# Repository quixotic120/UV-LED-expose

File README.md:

Controller board for a UV exposure box. Untested! Plan to support 2 layers of UV LEDs, 20x4 LCD, and a vacuum pump; ideally will be used for PCB exposure and solder mask curing.

completed:
board layout

to do:
test layout
firmware
plans for enclosure

if you try it let me know if it works!

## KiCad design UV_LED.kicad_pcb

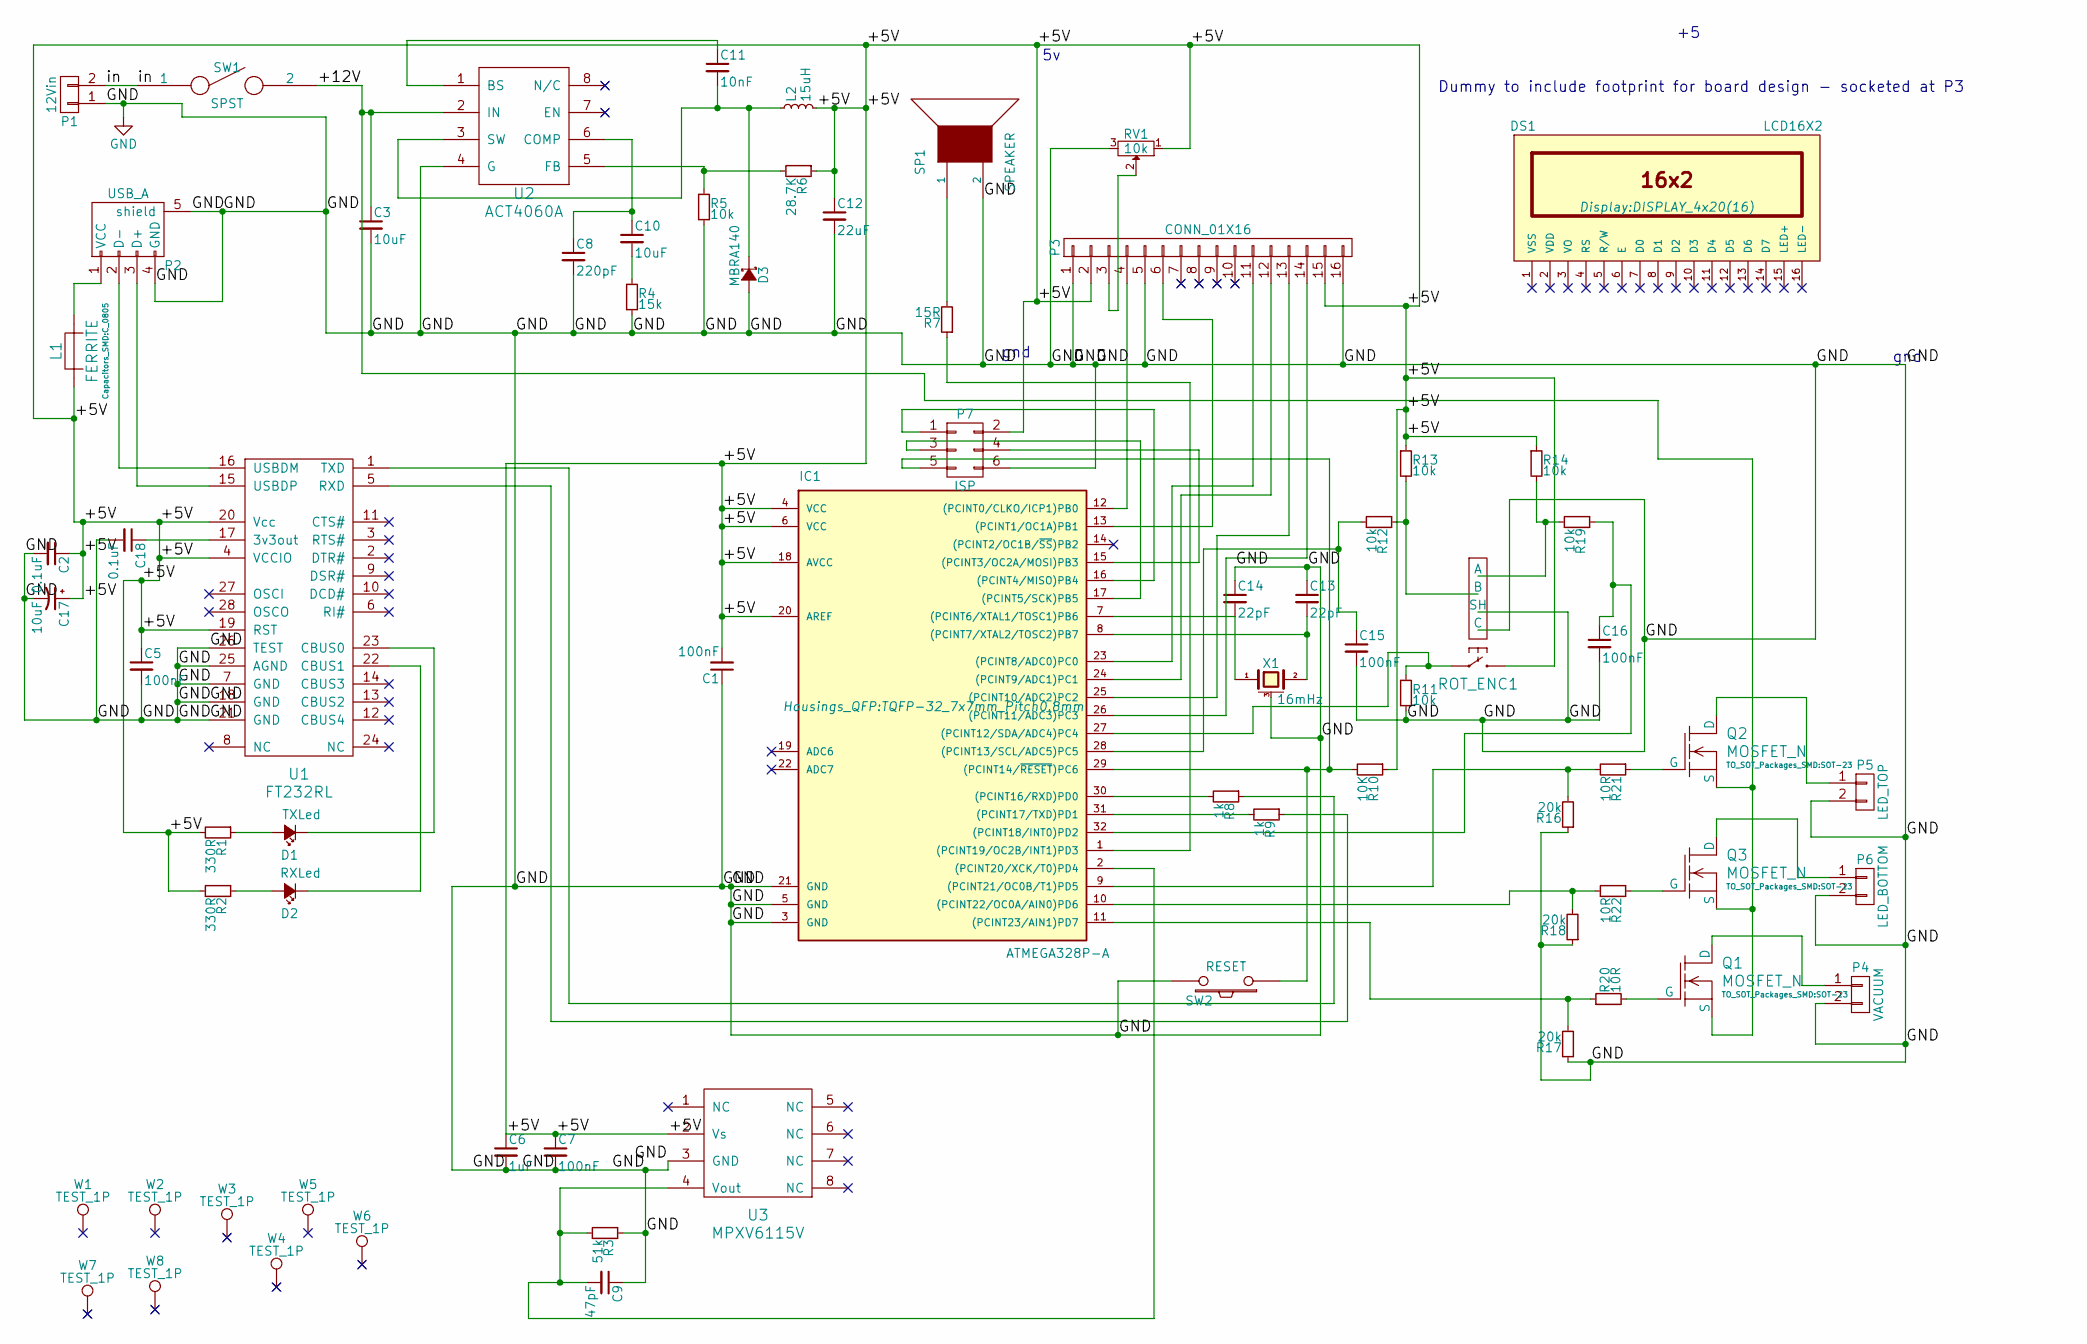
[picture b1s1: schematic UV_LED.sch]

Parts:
C1, C5, C7, C15, C16: 100nF; C_0805
C2, C18: 0.1uF; C_0805
C3, C10: 10uF; C_0805
C6: 1uF; C_0805
C8: 220pF; C_0805
C9: 47pF; C_0805
C11: 10nF; C_0805
C12: 22uF; C_0805
C13, C14: 22pF; C_0805
C17: 10uF; TantalC_SizeB_EIA-3528_Reflow
D1: TXLed; LED_0805
D2: RXLed; LED_0805
D3: MBRA140; DO-214AB
DS1: LCD16X2; DISPLAY_4x20(16)
IC1: ATMEGA328P-A; TQFP-32_7x7mm_Pitch0.8mm
L1: FERRITE; C_0805
L2: 15uH; C_0805
P1: 12Vin; Socket_MOLEX-KK-RM2-54mm_Lock_2pin_straight
P2: USB_A; USB_B
P3: CONN_01X16; Pin_Header_Angled_1x16_backward
P4: VACUUM; Socket_MOLEX-KK-RM2-54mm_Lock_2pin_straight
P5: LED_TOP; Socket_MOLEX-KK-RM2-54mm_Lock_2pin_straight
P6: LED_BOTTOM; Socket_MOLEX-KK-RM2-54mm_Lock_2pin_straight
P7: ISP; Pin_Header_Straight_2x03
Q1, Q2, Q3: MOSFET_N; SOT-23
R1, R2: 330R; R_0805
R3: 51k; R_0805
R4: 15k; R_0805
R5, R11, R12, R13, R14, R19: 10k; R_0805
R6: 28.7K; R_0805
R7: 15R; R_0805
R8, R9: 1k; R_0805
R10: 10K; R_0805
R16, R17, R18: 20k; R_0805
R20, R21, R22: 10R; R_0805
ROT_ENC1: AB2_ROTARY_ENCODER_W_SW; AB2_ROTARY_ENCODER_W_SWITCH
RV1: 10k; 35WR
SP1: SPEAKER; SMT-0540-S-R
SW1: SPST; Socket_MOLEX-KK-RM2-54mm_Lock_2pin_straight
SW2: RESET; Push_E-Switch_KS01Q01
U1: FT232RL; SSOP-28_5.3x10.2mm_Pitch0.65mm
U2: ACT4060A; SOIC-8_3.9x4.9mm_Pitch1.27mm
U3: MPXV6115V; SOIC-8_3.9x4.9mm_Pitch1.27mm
W1, W2, W7, W8: TEST_1P; MountingHole_2-5mm
W3, W4, W5, W6: TEST_1P; MountingHole_4mm
X1: 16mHz; Crystal_SMD_0603_4Pads

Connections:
/+5V: C1.2, C2.1, C5.1, C6.1, C7.1, C12.1, C17.1, IC1.4 (VCC), IC1.6 (VCC), IC1.18 (AVCC), IC1.20 (AREF), L1.1, L2.2, P3.2, P3.15, P7.2, R1.2, R2.2, R6.1, R10.1, R13.1, R14.1, ROT_ENC1.6, RV1.1, U1.4 (VCCIO), U1.19 (RST), U1.20 (Vcc), U3.2 (Vs)
/+12V: C3.1, Q1.2 (S), Q2.2 (S), Q3.2 (S), SW1.2, U2.2 (IN)
/in: P1.2, SW1.1
GND: C1.1, C2.2, C3.2, C5.2, C6.2, C7.2, C8.2, C9.1, C12.2, C13.1, C14.1, C15.2, C16.2, C17.2, C18.2, D3.2 (A), IC1.3 (GND), IC1.5 (GND), IC1.21 (GND), P1.1, P2.4 (GND), P2.5 (shield), P3.1, P3.5, P3.16, P4.2, P5.2, P6.2, P7.6, R3.1, R4.2, R5.2, R11.2, R16.1, R17.1, R18.1, ROT_ENC1.2 (C), ROT_ENC1.7 (SH), RV1.3, SP1.2, SW2.2, U1.7 (GND), U1.18 (GND), U1.21 (GND), U1.25 (AGND), U1.26 (TEST), U2.4 (G), U3.3 (GND), X1.3 (case)
unnamed: C9.2, IC1.2 ((PCINT20/XCK/T0)PD4), R3.2, U3.4 (Vout)
unnamed: C8.1, C10.1, U2.6 (COMP)
unnamed: C10.2, R4.1
unnamed: C11.1, U2.1 (BS)
unnamed: C11.2, D3.1 (K), L2.1, U2.3 (SW)
unnamed: C13.2, IC1.8 ((PCINT7/XTAL2/TOSC2)PB7), X1.2
unnamed: C14.2, IC1.7 ((PCINT6/XTAL1/TOSC1)PB6), X1.1
unnamed: C15.1, IC1.28 ((PCINT13/SCL/ADC5)PC5), R12.2
unnamed: C16.1, IC1.32 ((PCINT18/INT0)PD2), R19.1
unnamed: C18.1, U1.17 (3v3out)
unnamed: D1.1 (K), U1.23 (CBUS0)
unnamed: D1.2 (A), R1.1
unnamed: D2.1 (K), U1.22 (CBUS1)
unnamed: D2.2 (A), R2.1
unnamed: IC1.1 ((PCINT19/OC2B/INT1)PD3), R7.1
unnamed: IC1.9 ((PCINT21/OC0B/T1)PD5), R16.2, R21.2
unnamed: IC1.10 ((PCINT22/OC0A/AIN0)PD6), R18.2, R22.2
unnamed: IC1.11 ((PCINT23/AIN1)PD7), R17.2, R20.1
unnamed: IC1.12 ((PCINT0/CLKO/ICP1)PB0), P3.4
unnamed: IC1.13 ((PCINT1/OC1A)PB1), P3.6
unnamed: IC1.15 ((PCINT3/OC2A/MOSI)PB3), P7.4
unnamed: IC1.16 ((PCINT4/MISO)PB4), P7.1
unnamed: IC1.17 ((PCINT5/SCK)PB5), P7.3
unnamed: IC1.23 ((PCINT8/ADC0)PC0), P3.11
unnamed: IC1.24 ((PCINT9/ADC1)PC1), P3.12
unnamed: IC1.25 ((PCINT10/ADC2)PC2), P3.13
unnamed: IC1.26 ((PCINT11/ADC3)PC3), P3.14
unnamed: IC1.27 ((PCINT12/SDA/ADC4)PC4), R11.1, ROT_ENC1.4
unnamed: IC1.29 ((PCINT14/~RESET~)PC6), P7.5, R10.2, SW2.1
unnamed: IC1.30 ((PCINT16/RXD)PD0), R8.2
unnamed: IC1.31 ((PCINT17/TXD)PD1), R9.2
unnamed: L1.2, P2.1 (VCC)
unnamed: P2.2 (D-), U1.16 (USBDM)
unnamed: P2.3 (D+), U1.15 (USBDP)
unnamed: P3.3, RV1.2
unnamed: P4.1, Q1.3 (D)
unnamed: P5.1, Q2.3 (D)
unnamed: P6.1, Q3.3 (D)
unnamed: Q1.1 (G), R20.2
unnamed: Q2.1 (G), R21.1
unnamed: Q3.1 (G), R22.1
unnamed: R5.1, R6.2, U2.5 (FB)
unnamed: R7.2, SP1.1
unnamed: R8.1, U1.1 (TXD)
unnamed: R9.1, U1.5 (RXD)
unnamed: R12.1, R13.2, ROT_ENC1.3 (B)
unnamed: R14.2, R19.2, ROT_ENC1.1 (A)

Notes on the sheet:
Dummy to include footprint for board design - socketed at P3
gnd

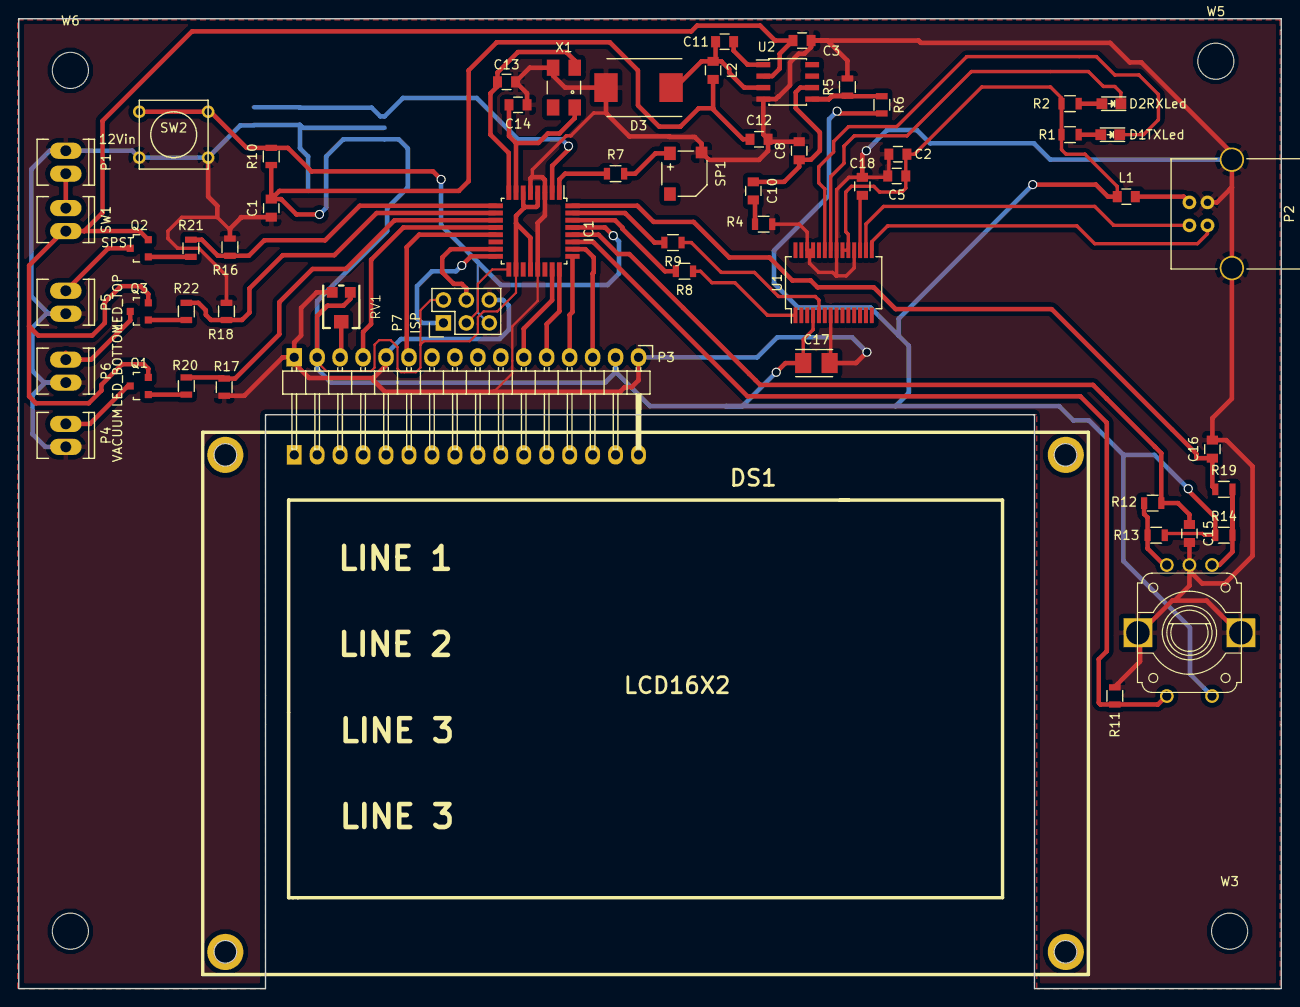
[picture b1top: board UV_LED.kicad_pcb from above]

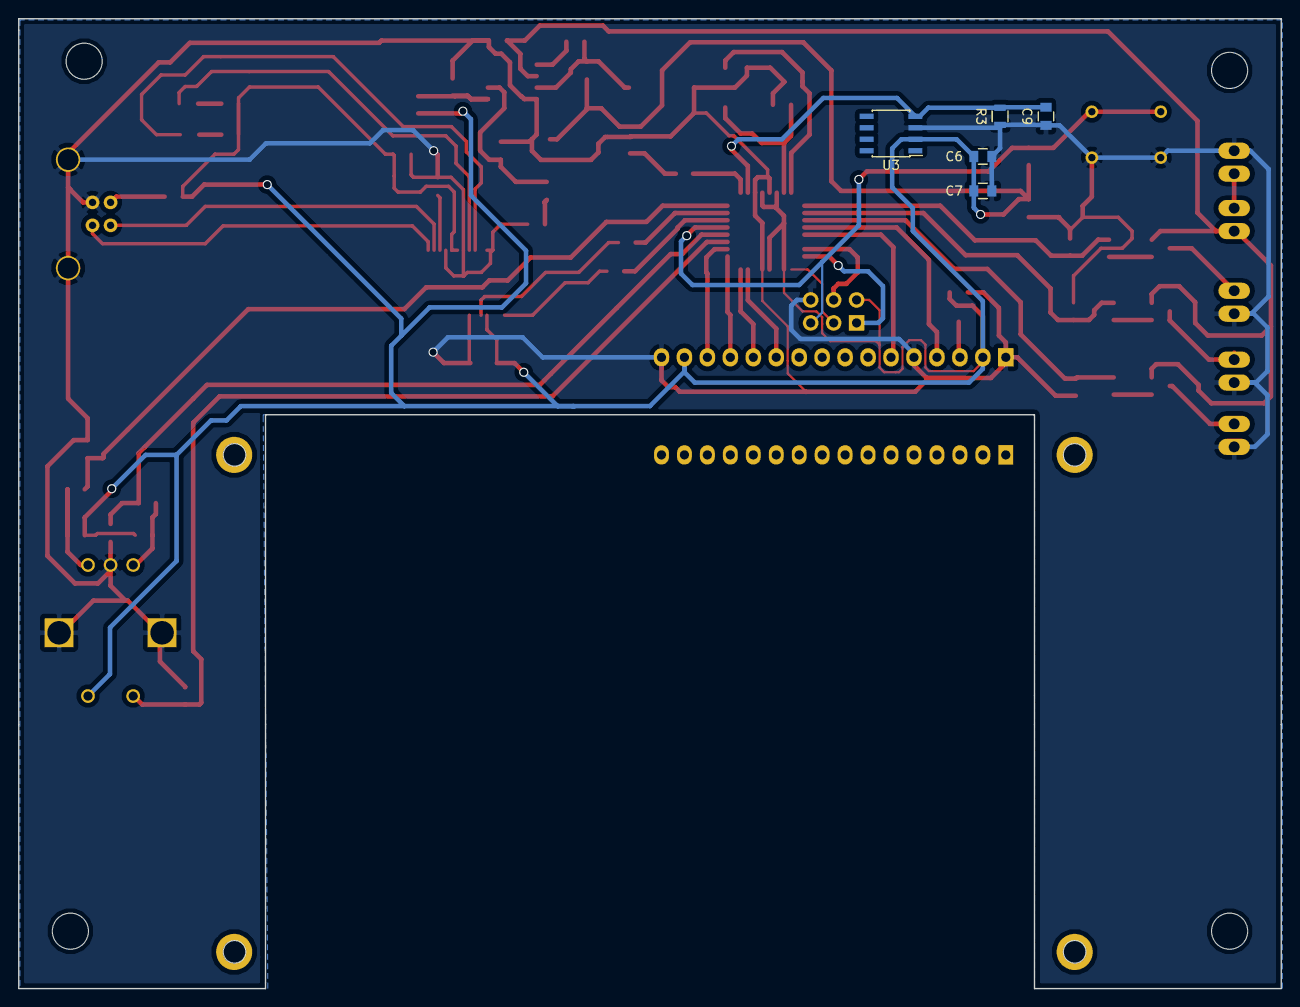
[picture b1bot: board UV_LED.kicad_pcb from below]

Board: 2 copper layers, 139.7 x 107.3 mm, 72 parts (5 on the bottom side), 51 nets.

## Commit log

2016-03-18 initial commit
    initial commit
2016-03-27 schematic changes, new pcb
    simplified the schematic, added reset button, remade pcb for easier
    home processing
2016-03-27 added renders, rerouted PCB
2016-03-28 renders
2016-03-30 gerbers
